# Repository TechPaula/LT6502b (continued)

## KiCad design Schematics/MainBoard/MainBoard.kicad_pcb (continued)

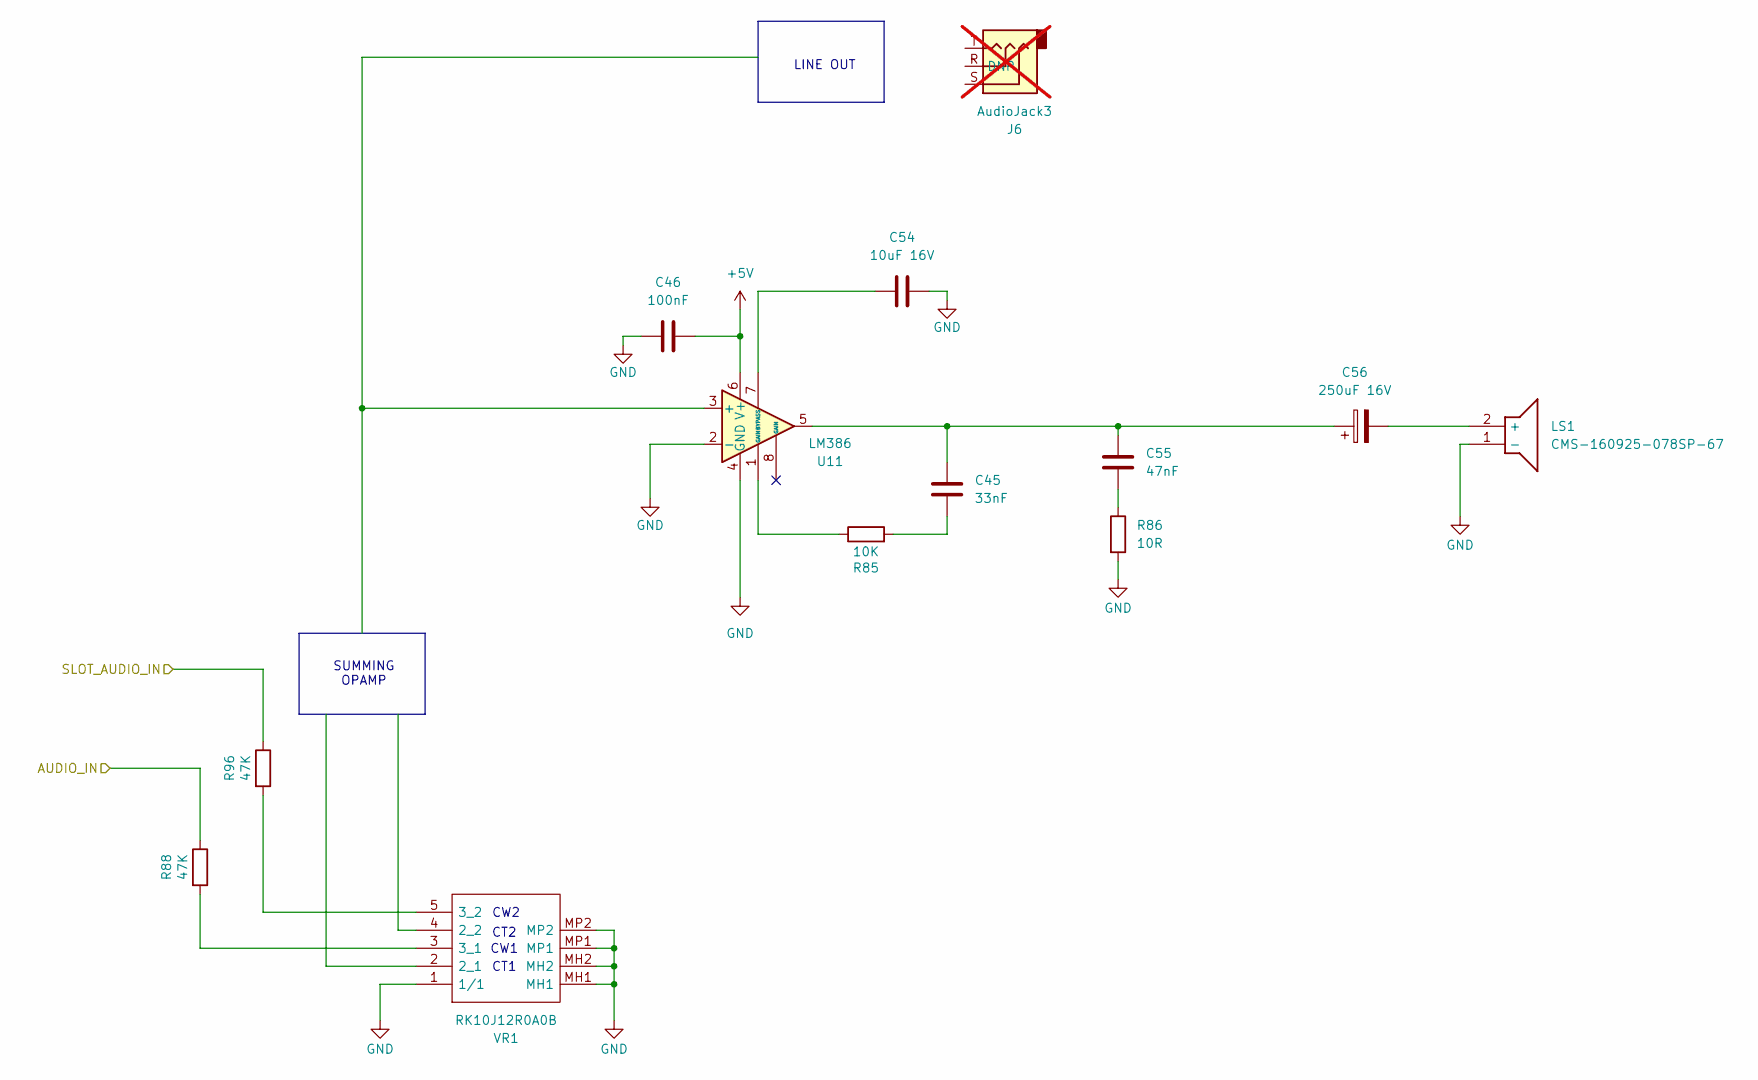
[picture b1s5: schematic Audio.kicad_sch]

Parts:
C45: 33nF; C_0603_1608Metric; LCSC C21117
C46: 100nF; C_0603_1608Metric; LCSC C113803
C54: 10uF 16V; C_0805_2012Metric; LCSC C15850
C55: 47nF; C_0603_1608Metric; LCSC C1622
C56: 250uF 16V; CP_Elec_10x12.5; Mouser Part Number 667-EEV-FK1V681Q
J6: AudioJack3; Jack_3.5mm_CUI_SJ-3524-SMT_Horizontal; LCSC DNP; not fitted
LS1: CMS-160925-078SP-67; CMS160925078SP67; Mouser Part Number 490-CMS160925078SP67
R85: 10K; R_0402_1005Metric; LCSC C25744
R86: 10R; R_0805_2012Metric; LCSC C844598
R88, R96: 47K; R_0402_1005Metric; LCSC DNF
U11: LM386; DIP-8_W7.62mm; Mouser Part Number 926-LM386N-3/NOPB
VR1: RK10J12R0A0B; Mouser Part Number 688-RK10J12R0A0B

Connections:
+5V: C46.2, U11.6 (V+); also elsewhere on the board
AUDIO: R88.1; also elsewhere on the board
GND: C46.1, C54.1, LS1.1 (-), R86.2, U11.2 (-), U11.4 (GND), VR1.1 (1/1), VR1.MH1, VR1.MH2, VR1.MP1, VR1.MP2; also elsewhere on the board
unnamed: C45.1, C55.1, C56.1, U11.5
unnamed: C45.2, R85.2
unnamed: C55.2, R86.1
unnamed: C56.2, LS1.2 (+)
unnamed: R85.1, U11.1 (GAIN)
unnamed: C54.2, U11.7 (BYPASS)
unnamed: R88.2, VR1.3 (3_1)
unnamed: R96.2, VR1.5 (3_2)
SLOT_AUDIO: R96.1; also elsewhere on the board

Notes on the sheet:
CT1
CT2
CW1
CW2
LINE OUT
SUMMING OPAMP

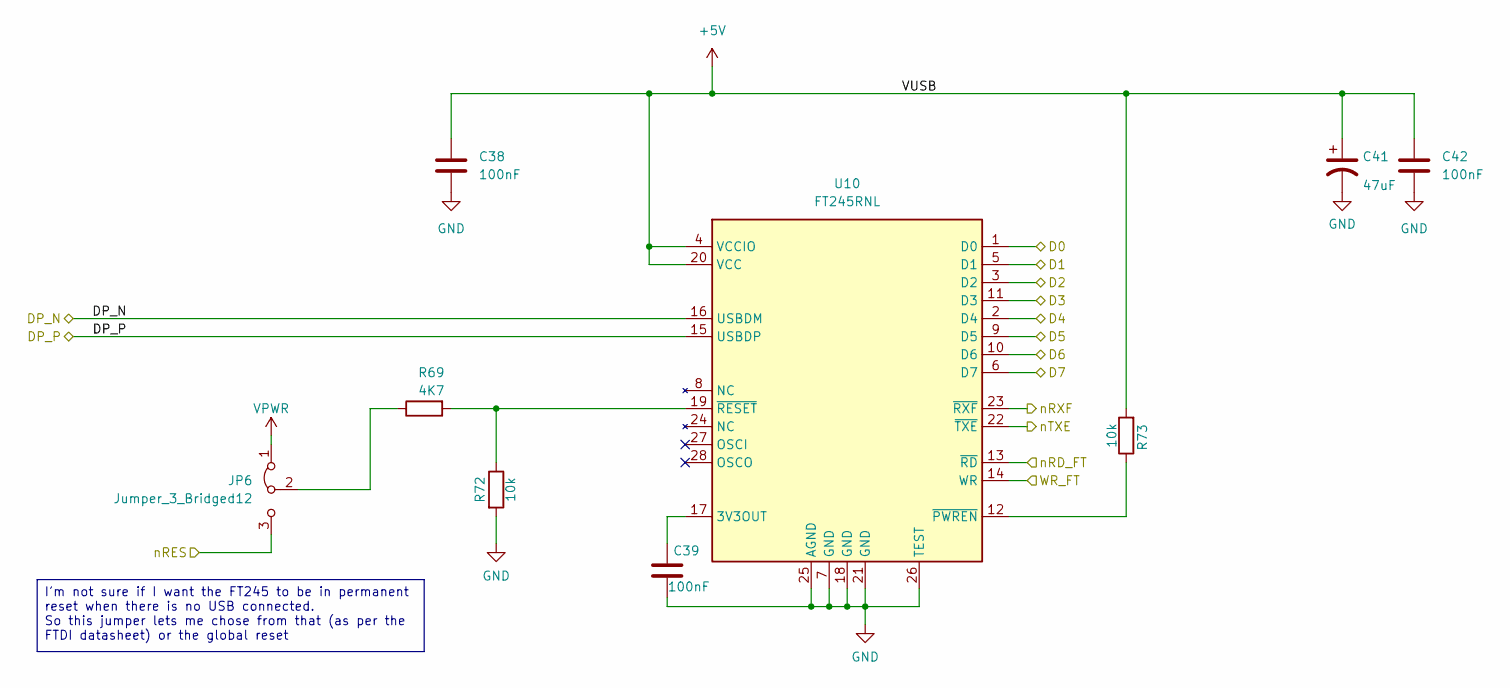
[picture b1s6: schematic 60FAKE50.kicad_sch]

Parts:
C38, C42: 100nF; C_0805_2012Metric; LCSC C49678
C39: 100nF; C_0603_1608Metric; LCSC C113803
C41: 47uF; C_1206_3216Metric; LCSC C22367835
JP6: Jumper_3_Bridged12; SolderJumper-3_P1.3mm_Bridged2Bar12_RoundedPad1.0x1.5mm
R69: 4K7; R_0402_1005Metric
R72, R73: 10k; R_0402_1005Metric; LCSC C25744
U10: FT245RNL; SSOP-28_5.3x10.2mm_P0.65mm; Mouser Part Number 895-FT245RNL-REEL; LCSC DNF

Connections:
+5V: C38.1, C41.1, C42.1, R73.2, U10.4 (VCCIO), U10.20 (VCC); also elsewhere on the board
/60FAKE50/nRES: JP6.3 (B)
/D0: U10.1 (D0); also elsewhere on the board
/D1: U10.5 (D1); also elsewhere on the board
/D2: U10.3 (D2); also elsewhere on the board
/D3: U10.11 (D3); also elsewhere on the board
/D4: U10.2 (D4); also elsewhere on the board
/D5: U10.9 (D5); also elsewhere on the board
/D6: U10.10 (D6); also elsewhere on the board
/D7: U10.6 (D7); also elsewhere on the board
DP_N: U10.16 (USBDM); also elsewhere on the board
DP_P: U10.15 (USBDP); also elsewhere on the board
GND: C38.2, C39.2, C41.2, C42.2, R72.2, U10.7 (GND), U10.18 (GND), U10.21 (GND), U10.25 (AGND), U10.26 (TEST); also elsewhere on the board
unnamed: JP6.2 (C), R69.1
unnamed: C39.1, U10.17 (3V3OUT)
unnamed: R73.1, U10.12 (~PWREN)
unnamed: R69.2, R72.1, U10.19 (~RESET)
VPWR: JP6.1 (A); also elsewhere on the board
WR_FT: U10.14 (WR); also elsewhere on the board
nRD_FT: U10.13 (~RD); also elsewhere on the board
nRXF: U10.23 (~RXF); also elsewhere on the board
nTXE: U10.22 (~TXE); also elsewhere on the board

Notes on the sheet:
I'm not sure if I want the FT245 to be in permanent reset when there is no USB connected. So this jumper lets me chose from that (as per the FTDI datasheet) or the global reset

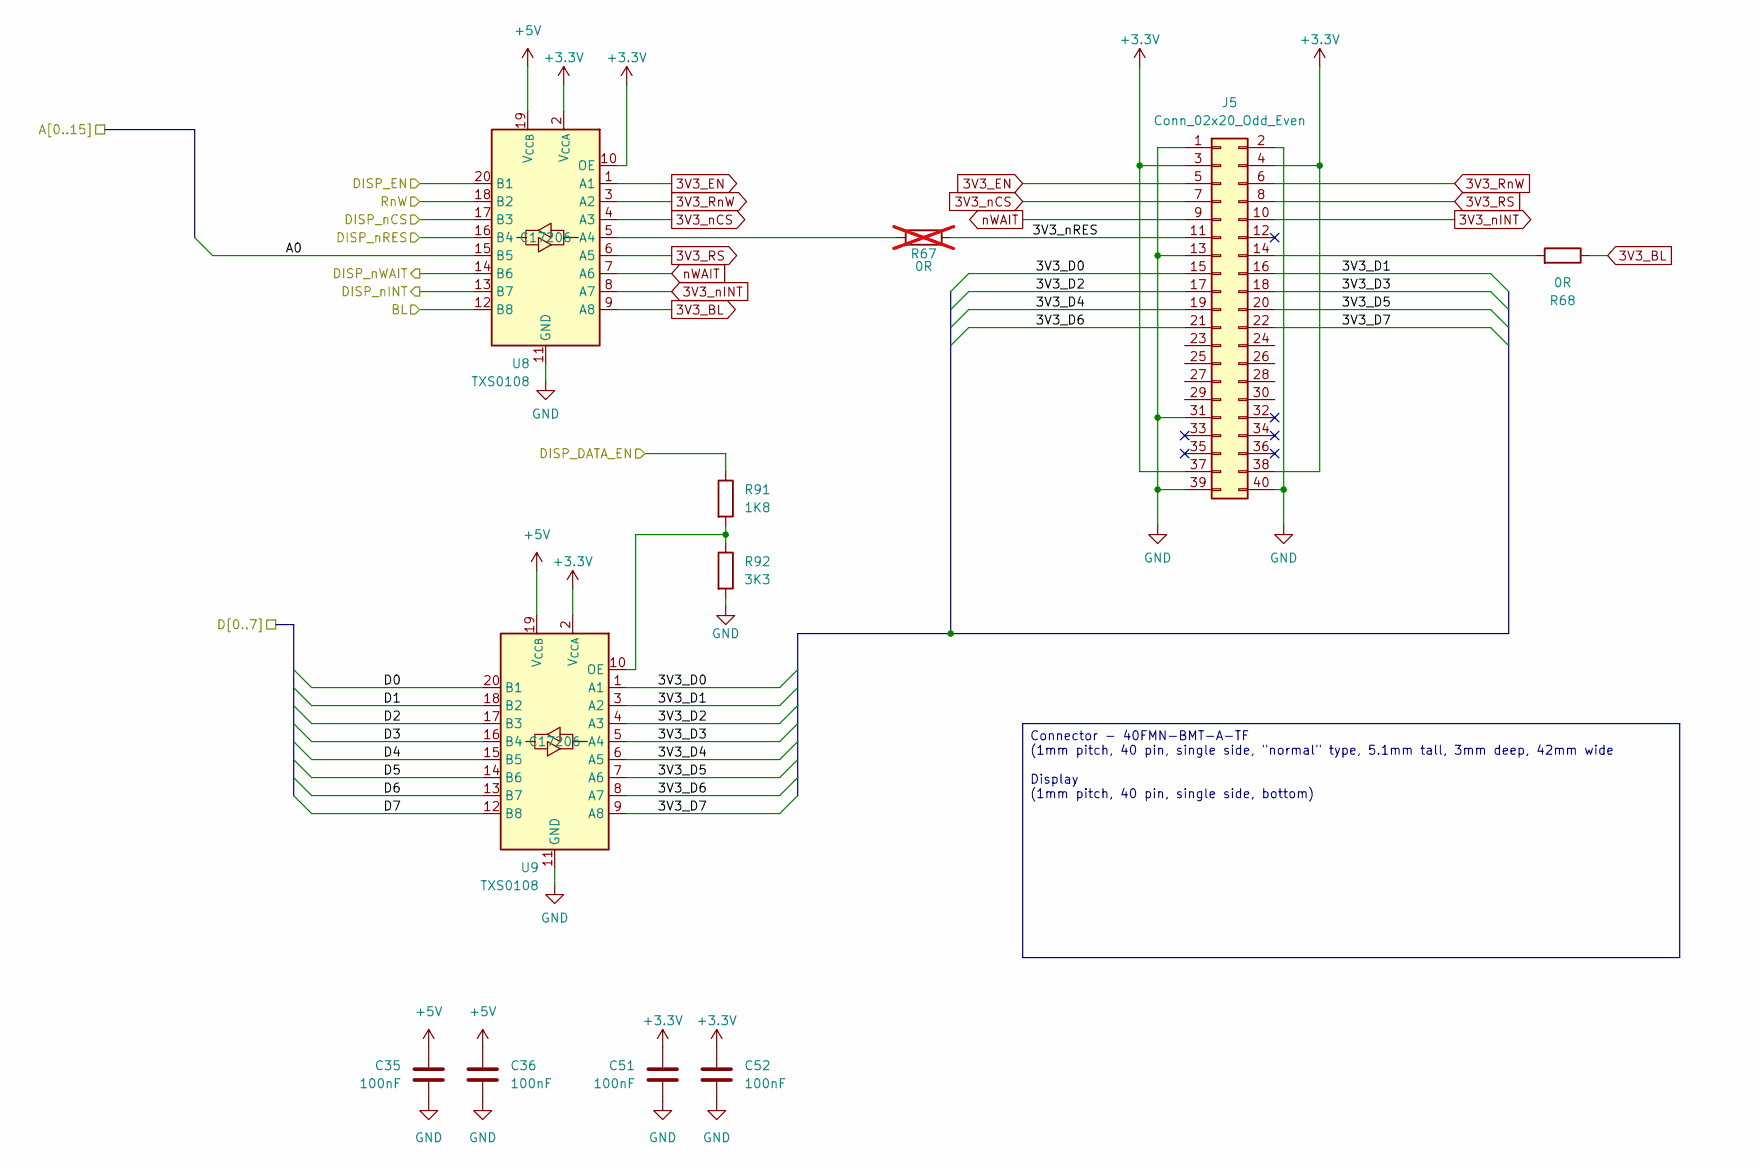
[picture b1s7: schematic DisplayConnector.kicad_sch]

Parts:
C35, C36, C51, C52: 100nF; C_0603_1608Metric; LCSC C113803
J5: Conn_02x20_Odd_Even; GCT_FFC3B07-40-T; LCSC DNF
R67: 0R; R_0402_1005Metric; LCSC DNF; not fitted
R68: 0R; R_0402_1005Metric; LCSC DNF
R91: 1K8; R_0603_1608Metric; LCSC C25890
R92: 3K3; R_0603_1608Metric; LCSC C25890
U8, U9: TXS0108; TSSOP-20_4.4x6.5mm_P0.65mm; Mouser Part Number 595-TXB0108PWR; LCSC C17206

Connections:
3V3_BL: R68.1, U8.9 (A8)
3V3_EN: J5.5, U8.1 (A1)
3V3_RS: J5.8, U8.6 (A5)
3V3_RnW: J5.6, U8.3 (A2)
3V3_nCS: J5.7, U8.4 (A3)
3V3_nINT: J5.10, U8.8 (A7)
+3.3V: C51.1, C52.1, J5.3, J5.4, J5.37, J5.38, U8.2 (V_{CCA}), U8.10 (OE), U9.2 (V_{CCA}); also elsewhere on the board
+5V: C35.1, C36.1, U8.19 (V_{CCB}), U9.19 (V_{CCB}); also elsewhere on the board
/A0: U8.15 (B5); also elsewhere on the board
/D0: U9.20 (B1); also elsewhere on the board
/D1: U9.18 (B2); also elsewhere on the board
/D2: U9.17 (B3); also elsewhere on the board
/D3: U9.16 (B4); also elsewhere on the board
/D4: U9.15 (B5); also elsewhere on the board
/D5: U9.14 (B6); also elsewhere on the board
/D6: U9.13 (B7); also elsewhere on the board
/D7: U9.12 (B8); also elsewhere on the board
/Display Connector/3V3_D0: J5.15, U9.1 (A1)
/Display Connector/3V3_D1: J5.16, U9.3 (A2)
/Display Connector/3V3_D2: J5.17, U9.4 (A3)
/Display Connector/3V3_D3: J5.18, U9.5 (A4)
/Display Connector/3V3_D4: J5.19, U9.6 (A5)
/Display Connector/3V3_D5: J5.20, U9.7 (A6)
/Display Connector/3V3_D6: J5.21, U9.8 (A7)
/Display Connector/3V3_D7: J5.22, U9.9 (A8)
/Display Connector/3V3_nRES: J5.11, R67.2
/Display Connector/BL: U8.12 (B8); also elsewhere on the board
/Display Connector/DISP_DATA_EN: R91.1; also elsewhere on the board
/Display Connector/DISP_EN: U8.20 (B1); also elsewhere on the board
/Display Connector/DISP_nCS: U8.17 (B3); also elsewhere on the board
/Display Connector/DISP_nINT: U8.13 (B7); also elsewhere on the board
/Display Connector/DISP_nRES: U8.16 (B4); also elsewhere on the board
/Display Connector/DISP_nWAIT: U8.14 (B6); also elsewhere on the board
GND: C35.2, C36.2, C51.2, C52.2, J5.1, J5.2, J5.13, J5.31, J5.39, J5.40, R92.2, U8.11 (GND), U9.11 (GND); also elsewhere on the board
unnamed: J5.14, R68.2
unnamed: R67.1, U8.5 (A4)
unnamed: R91.2, R92.1, U9.10 (OE)
RnW: U8.18 (B2); also elsewhere on the board
nWAIT: J5.9, U8.7 (A6)

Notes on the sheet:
Connector - 40FMN-BMT-A-TF (1mm pitch, 40 pin, single side, "normal" type, 5.1mm tall, 3mm deep, 42mm wide Display (1mm pitch, 40 pin, single side, bottom)

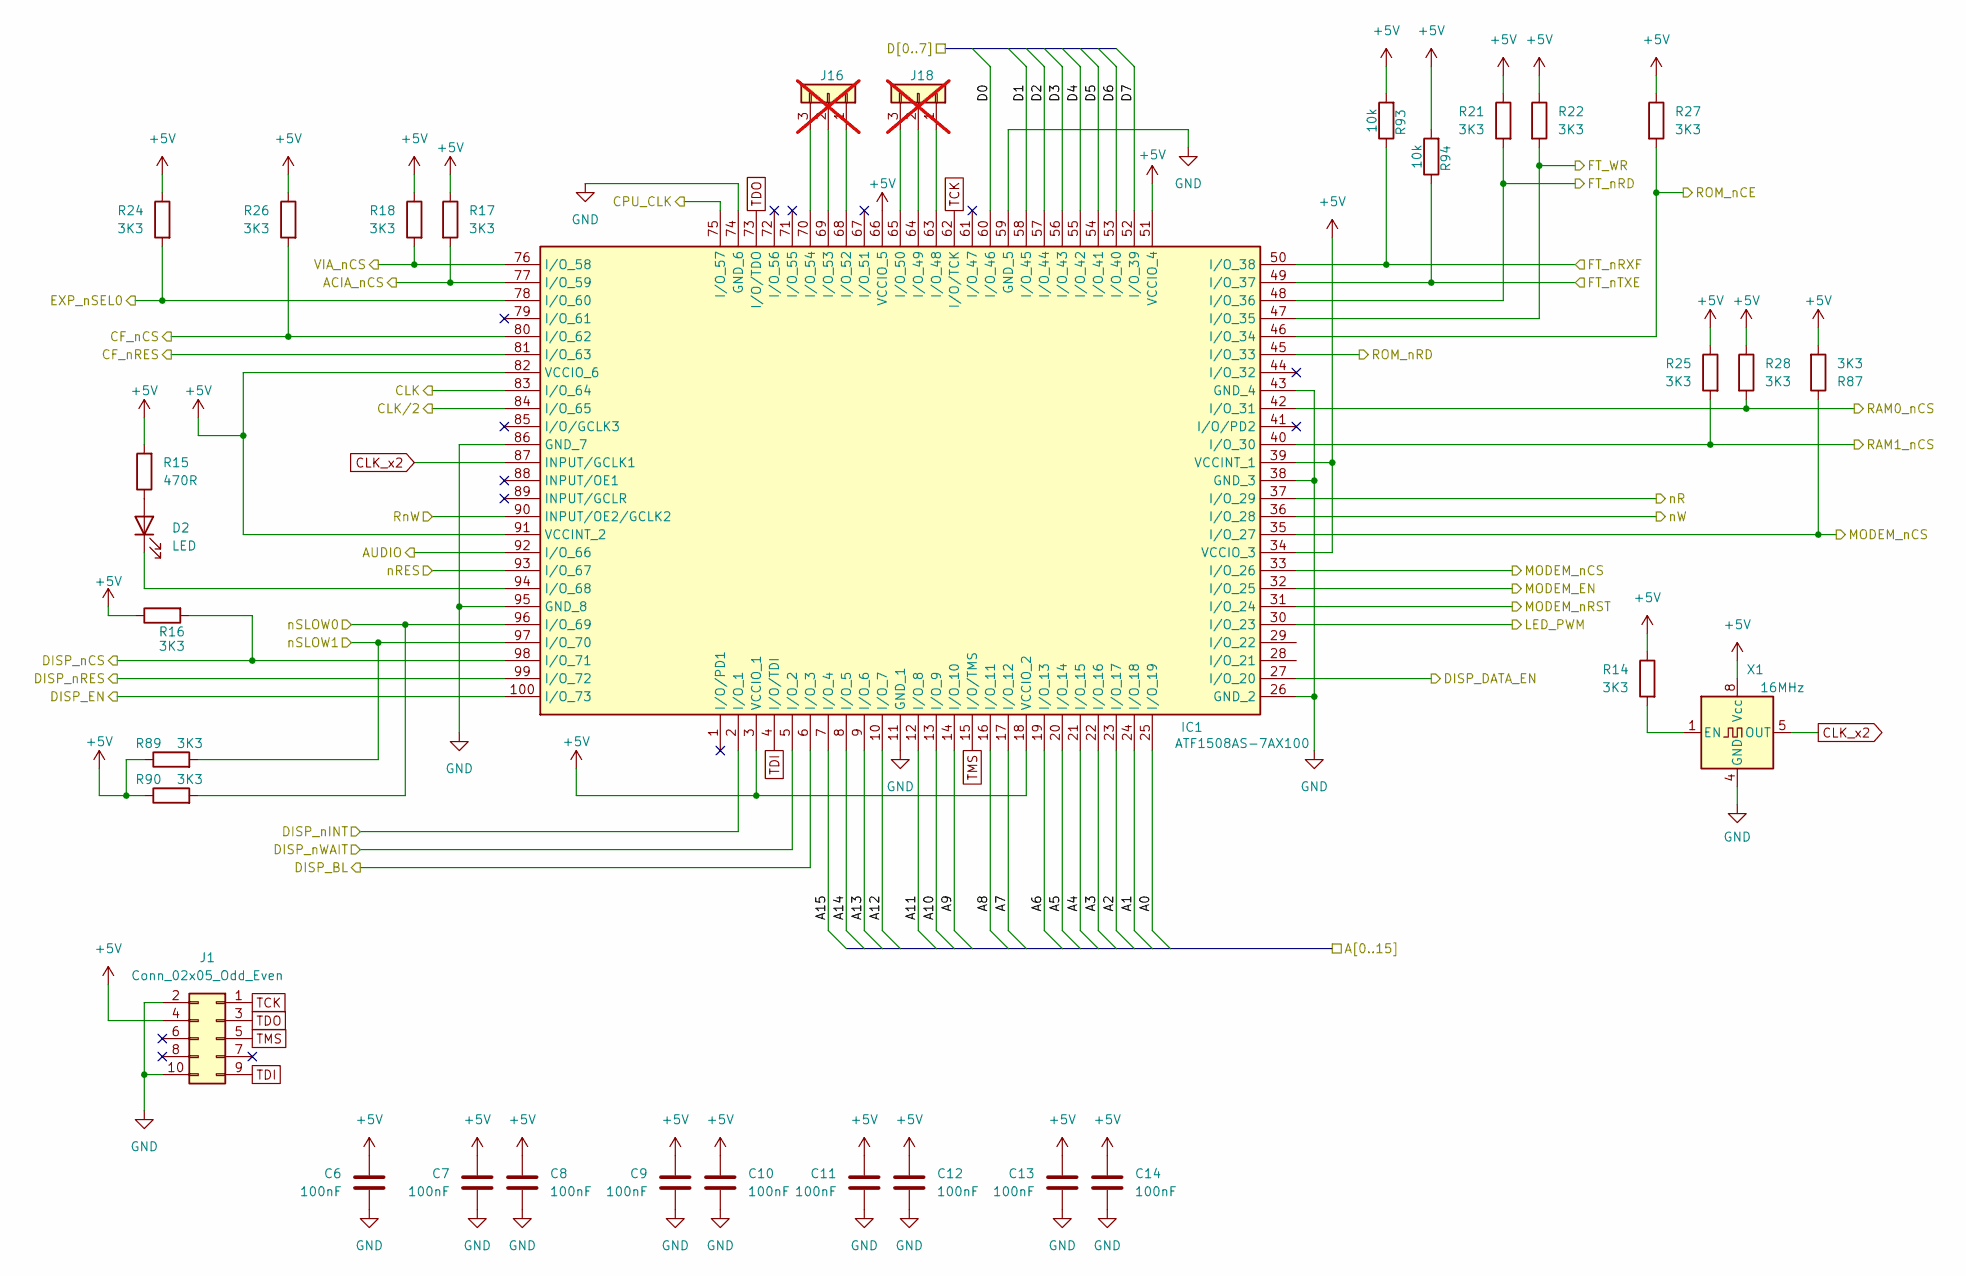
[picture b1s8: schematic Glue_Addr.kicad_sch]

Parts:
C6, C7, C8, C9, C11, C12, C13, C14: 100nF; C_0603_1608Metric; LCSC C113803
C10: 100nF; C_0402_1005Metric; LCSC C1581
D2: LED; LED_0603_1608Metric; LCSC DNF
IC1: ATF1508AS-7AX100; QFP50P1600X1600X120-100N; Mouser Part Number 556-AF1508AS7AX100
J1: Conn_02x05_Odd_Even; PinHeader_2x05_P2.54mm_Vertical; LCSC DNF
J16, J18: Conn_01x03; PinHeader_1x03_P1.00mm_Vertical_SMD_Pin1Left; LCSC DNF; not fitted
R14, R16, R17, R18, R21, R22, R24, R25, R26, R27, R28, R87, R89, R90: 3K3; R_0402_1005Metric; LCSC C25890
R15: 470R; R_0402_1005Metric; LCSC C25117
R93, R94: 10k; R_0402_1005Metric; LCSC C25744
X1: 16MHz; Oscillator_DIP-8; Mouser Part Number 520-2100AX-283.2; LCSC DNF

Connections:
+5V: C6.1, C7.1, C8.1, C9.1, C10.1, C11.1, C12.1, C13.1, C14.1, IC1.3 (VCCIO_1), IC1.18 (VCCIO_2), IC1.34 (VCCIO_3), IC1.39 (VCCINT_1), IC1.51 (VCCIO_4), IC1.66 (VCCIO_5), IC1.82 (VCCIO_6), IC1.91 (VCCINT_2), J1.4, R14.1, R15.2, R16.1, R17.1, R18.1, R21.1, R22.1, R24.1, R25.1, R26.1, R27.1, R28.1, R87.2, R89.1, R90.1, R93.2, R94.2, X1.8 (Vcc); also elsewhere on the board
/A0: IC1.25 (I/O_19); also elsewhere on the board
/A1: IC1.24 (I/O_18); also elsewhere on the board
/A2: IC1.23 (I/O_17); also elsewhere on the board
/A3: IC1.22 (I/O_16); also elsewhere on the board
/A4: IC1.21 (I/O_15); also elsewhere on the board
/A5: IC1.20 (I/O_14); also elsewhere on the board
/A6: IC1.19 (I/O_13); also elsewhere on the board
/A7: IC1.17 (I/O_12); also elsewhere on the board
/A8: IC1.16 (I/O_11); also elsewhere on the board
/A9: IC1.14 (I/O_10); also elsewhere on the board
/A10: IC1.13 (I/O_9); also elsewhere on the board
/A11: IC1.12 (I/O_8); also elsewhere on the board
/A12: IC1.10 (I/O_7); also elsewhere on the board
/A13: IC1.9 (I/O_6); also elsewhere on the board
/A14: IC1.8 (I/O_5); also elsewhere on the board
/A15: IC1.7 (I/O_4); also elsewhere on the board
/D0: IC1.60 (I/O_46); also elsewhere on the board
/D1: IC1.58 (I/O_45); also elsewhere on the board
/D2: IC1.57 (I/O_44); also elsewhere on the board
/D3: IC1.56 (I/O_43); also elsewhere on the board
/D4: IC1.55 (I/O_42); also elsewhere on the board
/D5: IC1.54 (I/O_41); also elsewhere on the board
/D6: IC1.53 (I/O_40); also elsewhere on the board
/D7: IC1.52 (I/O_39); also elsewhere on the board
/Display Connector/BL: IC1.6 (I/O_3); also elsewhere on the board
/Display Connector/DISP_DATA_EN: IC1.27 (I/O_20); also elsewhere on the board
/Display Connector/DISP_EN: IC1.100 (I/O_73); also elsewhere on the board
/Display Connector/DISP_nCS: IC1.98 (I/O_71), R16.2; also elsewhere on the board
/Display Connector/DISP_nINT: IC1.2 (I/O_1); also elsewhere on the board
/Display Connector/DISP_nRES: IC1.99 (I/O_72); also elsewhere on the board
/Display Connector/DISP_nWAIT: IC1.5 (I/O_2); also elsewhere on the board
ACIA_nCS: IC1.77 (I/O_59), R17.2; also elsewhere on the board
AUDIO: IC1.92 (I/O_66); also elsewhere on the board
CFnRES: IC1.80 (I/O_62), R26.2; also elsewhere on the board
CLK: IC1.83 (I/O_64); also elsewhere on the board
CLK_x2: IC1.87 (INPUT/GCLK1), X1.5 (OUT)
CLK/2: IC1.84 (I/O_65); also elsewhere on the board
CPU_CLK: IC1.75 (I/O_57); also elsewhere on the board
EXP_nSEL0: IC1.78 (I/O_60), R24.2; also elsewhere on the board
GND: C6.2, C7.2, C8.2, C9.2, C10.2, C11.2, C12.2, C13.2, C14.2, IC1.11 (GND_1), IC1.26 (GND_2), IC1.38 (GND_3), IC1.43 (GND_4), IC1.59 (GND_5), IC1.74 (GND_6), IC1.86 (GND_7), IC1.95 (GND_8), J1.2, J1.10, X1.4 (GND); also elsewhere on the board
KEYLED_PWM: IC1.30 (I/O_23); also elsewhere on the board
MODEM_EN: IC1.32 (I/O_25); also elsewhere on the board
MODEM_nCS: IC1.33 (I/O_26), IC1.35 (I/O_27), R87.1; also elsewhere on the board
MODEM_nRST: IC1.31 (I/O_24); also elsewhere on the board
unnamed: D2.2 (A), R15.1
unnamed: D2.1 (K), IC1.94 (I/O_68)
unnamed: IC1.63 (I/O_48), J18.1
unnamed: IC1.64 (I/O_49), J18.2
unnamed: IC1.65 (I/O_50), J18.3
unnamed: IC1.68 (I/O_52), J16.1
unnamed: IC1.69 (I/O_53), J16.2
unnamed: IC1.70 (I/O_54), J16.3
unnamed: R14.2, X1.1 (EN)
ROM_nCE: IC1.46 (I/O_34), R27.2; also elsewhere on the board
ROM_nR: IC1.45 (I/O_33); also elsewhere on the board
RnW: IC1.90 (INPUT/OE2/GCLK2); also elsewhere on the board
TCK: IC1.62 (I/O/TCK), J1.1
TDI: IC1.4 (I/O/TDI), J1.9
TDO: IC1.73 (I/O/TDO), J1.3
TMS: IC1.15 (I/O/TMS), J1.5
VIA_nCS: IC1.76 (I/O_58), R18.2; also elsewhere on the board
WR_FT: IC1.47 (I/O_35), R22.2; also elsewhere on the board
nCF_CS0: IC1.81 (I/O_63); also elsewhere on the board
nR: IC1.37 (I/O_29); also elsewhere on the board
nRAM0_CS: IC1.42 (I/O_31), R28.2; also elsewhere on the board
nRAM1_CS: IC1.40 (I/O_30), R25.2; also elsewhere on the board
nRD_FT: IC1.48 (I/O_36), R21.2; also elsewhere on the board
nRES: IC1.93 (I/O_67); also elsewhere on the board
nRXF: IC1.49 (I/O_37), R94.1; also elsewhere on the board
nSLOW0: IC1.96 (I/O_69), R90.2; also elsewhere on the board
nSLOW1: IC1.97 (I/O_70), R89.2; also elsewhere on the board
nTXE: IC1.50 (I/O_38), R93.1; also elsewhere on the board
nW: IC1.36 (I/O_28); also elsewhere on the board

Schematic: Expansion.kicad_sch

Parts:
C43: 100nF; C_0603_1608Metric; LCSC C113803
C44: 22uF 25V; C_0805_2012Metric; LCSC C45783
D19, D21: 1N4148; D_DO-35_SOD27_P7.62mm_Horizontal; LCSC DNF
J10: Conn_02x20_Odd_Even; PinHeader_2x20_P2.54mm_Horizontal

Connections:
+5V: C43.1, C44.1, J10.1, J10.2, J10.3, J10.4; also elsewhere on the board
/A0: J10.5; also elsewhere on the board
/A1: J10.6; also elsewhere on the board
/A2: J10.7; also elsewhere on the board
/A3: J10.8; also elsewhere on the board
/A4: J10.9; also elsewhere on the board
/A5: J10.10; also elsewhere on the board
/A6: J10.11; also elsewhere on the board
/A7: J10.12; also elsewhere on the board
/D0: J10.13; also elsewhere on the board
/D1: J10.14; also elsewhere on the board
/D2: J10.15; also elsewhere on the board
/D3: J10.16; also elsewhere on the board
/D4: J10.17; also elsewhere on the board
/D5: J10.18; also elsewhere on the board
/D6: J10.19; also elsewhere on the board
/D7: J10.20; also elsewhere on the board
CLK: J10.28; also elsewhere on the board
CLK/2: J10.30; also elsewhere on the board
CPU_CLK: J10.23; also elsewhere on the board
EXP_nSEL0: J10.31; also elsewhere on the board
GND: C43.2, C44.2, J10.37, J10.38, J10.39, J10.40; also elsewhere on the board
unnamed: D19.1 (K), J10.27
unnamed: D21.1 (K), J10.29
RnW: J10.24; also elsewhere on the board
SLOT_AUDIO: J10.36; also elsewhere on the board
nIRQ: J10.32; also elsewhere on the board
nRES: J10.33; also elsewhere on the board
nSLOW0: D19.2 (A); also elsewhere on the board
nSLOW1: D21.2 (A); also elsewhere on the board

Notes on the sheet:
I should have routed CLK/2 to the VIA/ACIA instead of the 16MHz Clock So I've swapped them in the CPLD.
Much simplified from first laptop This is solely for expansion now and not an alternative CPU

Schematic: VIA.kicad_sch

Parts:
C47: 100nF; C_0402_1005Metric; LCSC C113803
D16: 1N4148W; D_SOD-123; LCSC C2099
IC3: W65C22S6TQG-14; QFP80P1320X1320X270-44N; Mouser Part Number 955-W65C22S6TQG-14
J9: Conn_02x02_Odd_Even; PinHeader_2x02_P1.27mm_Vertical_SMD
J12, J13: Conn_02x06_Odd_Even; PinSocket_2x06_P2.54mm_Horizontal; LCSC DNF

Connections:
+5V: C47.1, IC3.15 (VDD), IC3.20 (CS1), J12.1, J12.2, J13.1, J13.2; also elsewhere on the board
/A0: IC3.36 (RS0); also elsewhere on the board
/A1: IC3.35 (RS1); also elsewhere on the board
/A2: IC3.34 (RS2); also elsewhere on the board
/A3: IC3.33 (RS3); also elsewhere on the board
/D0: IC3.30 (D0); also elsewhere on the board
/D1: IC3.29 (D1); also elsewhere on the board
/D2: IC3.28 (D2); also elsewhere on the board
/D3: IC3.26 (D3); also elsewhere on the board
/D4: IC3.25 (D4); also elsewhere on the board
/D5: IC3.24 (D5); also elsewhere on the board
/D6: IC3.23 (D6); also elsewhere on the board
/D7: IC3.22 (D7); also elsewhere on the board
/VIA/VA_CA1: IC3.37 (CA2), J9.1; also elsewhere on the board
/VIA/VA_CA2: IC3.38 (CA1), J9.3; also elsewhere on the board
/VIA/VA_CB1: IC3.13 (CB1), J9.2; also elsewhere on the board
/VIA/VA_CB2: IC3.14 (CB2), J9.4; also elsewhere on the board
/VIA/VA_PA0: IC3.40 (PA0), J13.11
/VIA/VA_PA1: IC3.41 (PA1), J13.9
/VIA/VA_PA2: IC3.42 (PA2), J13.7
/VIA/VA_PA3: IC3.43 (PA3), J13.5
/VIA/VA_PA4: IC3.44 (PA4), J13.12
/VIA/VA_PA5: IC3.1 (PA5), J13.10
/VIA/VA_PA6: IC3.2 (PA6), J13.8
/VIA/VA_PA7: IC3.3 (PA7), J13.6
/VIA/VA_PB0: IC3.4 (PB0), J12.11
/VIA/VA_PB1: IC3.6 (PB1), J12.9
/VIA/VA_PB2: IC3.7 (PB2), J12.7
/VIA/VA_PB3: IC3.8 (PB3), J12.5
/VIA/VA_PB4: IC3.9 (PB4), J12.12
/VIA/VA_PB5: IC3.10 (PB5), J12.10
/VIA/VA_PB6: IC3.11 (PB6), J12.8
/VIA/VA_PB7: IC3.12 (PB7), J12.6
CLK: IC3.21 (PHI2); also elsewhere on the board
GND: C47.2, IC3.39 (VSS), J12.3, J12.4, J13.3, J13.4; also elsewhere on the board
unnamed: D16.1 (K), IC3.17 (IRQB)
RnW: IC3.18 (IRWB); also elsewhere on the board
VIA_nCS: IC3.19 (CS2B); also elsewhere on the board
nIRQ: D16.2 (A); also elsewhere on the board
nRES: IC3.31 (RESB); also elsewhere on the board

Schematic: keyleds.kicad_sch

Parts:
D17: LED; LED_D5.0mm; LCSC DNF
D56, D60, D61, D62, D63, D64, D65, D66, D67, D68: LED; LED_0603_1608Metric; LCSC C3030991
JP4: Jumper_3_Bridged12; SolderJumper-3_P1.3mm_Bridged2Bar12_RoundedPad1.0x1.5mm
JP5: Jumper_2_Open; SolderJumper-2_P1.3mm_Open_TrianglePad1.0x1.5mm; LCSC DNF
R70: 470R; R_0603_1608Metric_Pad0.98x0.95mm_HandSolder; LCSC DNF
R107, R115, R116, R117, R118, R119, R120, R121, R122, R123: 330R; R_0603_1608Metric_Pad0.98x0.95mm_HandSolder; LCSC DNF

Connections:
+5V: JP4.3 (B); also elsewhere on the board
/Keyboard IF/KEY_LEDs/LED_PWM: D56.2 (A), D60.2 (A), D61.2 (A), D62.2 (A), D63.2 (A), D64.2 (A), JP4.1 (A), JP5.1 (A); also elsewhere on the board
GND: R107.1, R115.1, R116.1, R117.1, R118.1, R119.1, R120.1, R121.1, R122.1, R123.1; also elsewhere on the board
KEYLED0: D17.1 (K); also elsewhere on the board
unnamed: D17.2 (A), R70.2
unnamed: D56.1 (K), R107.2
unnamed: D60.1 (K), R115.2
unnamed: D61.1 (K), R116.2
unnamed: D62.1 (K), R117.2
unnamed: D63.1 (K), R118.2
unnamed: D64.1 (K), R119.2
unnamed: D65.2 (A), D66.2 (A), D67.2 (A), D68.2 (A), JP5.2 (B)
unnamed: D65.1 (K), R120.2
unnamed: D66.1 (K), R121.2
unnamed: D67.1 (K), R122.2
unnamed: D68.1 (K), R123.2
unnamed: JP4.2 (C), R70.1

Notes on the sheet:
LEFT
ENTER
SHIFT
RIGHT
BREAK
BACKSPACE
CTRL
DOWN

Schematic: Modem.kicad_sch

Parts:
C60, C62, C63: 100nF; C_0402_1005Metric; LCSC C113803
C61: 47uF; C_1206_3216Metric; LCSC C96123
R97, R98, R101, R104: 10K; R_0402_1005Metric; LCSC DNF; not fitted
R99, R102: 1K8; R_0603_1608Metric; LCSC C25890
R100, R103: 3K3; R_0603_1608Metric; LCSC C25890
R105, R106: 0R; R_0603_1608Metric
U13: ESP8266-01_ESP-01; XCVR_ESP8266-01_ESP-01; PARTREV V1.2
U14: TXS0102DCT; SSOP-8_2.95x2.8mm_P0.65mm

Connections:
+3.3V: C60.1, C61.1, C62.1, R97.1, R98.1, U13.8 (VCC), U14.3 (VCCA), U14.6 (OE); also elsewhere on the board
+5V: C63.1, R101.1, R104.1, U14.7 (VCCB); also elsewhere on the board
/Keyboard IF/Modem/RX_3V3: R98.2, U13.4 (RXD), U14.4 (A2)
/Keyboard IF/Modem/TX_3V3: R97.2, U13.5 (TXD), U14.5 (A1)
GND: C60.2, C61.2, C62.2, C63.2, R100.2, R103.2, U13.1 (GND), U14.2 (GND); also elsewhere on the board
MODEM_EN: R99.1; also elsewhere on the board
MODEM_SER_IN: R105.2; also elsewhere on the board
MODEM_SER_OUT: R106.2; also elsewhere on the board
MODEM_nRST: R102.1; also elsewhere on the board
unnamed: R99.2, R100.1, U13.6 (EN)
unnamed: R102.2, R103.1, U13.7 (~RST)
unnamed: R101.2, R105.1, U14.8 (B1)
unnamed: R104.2, R106.1, U14.1 (B2)

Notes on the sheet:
Place to allow RX/TX swap

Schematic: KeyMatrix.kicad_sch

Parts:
D1, D12, D13, D14, D15, D20, D22, D23, D24, D25, D26, D27, D28, D29, D30, D31, D32, D33, D34, D35, D36, D37, D38, D39, D40, D41, D42, D43, D44, D45, D46, D47, D48, D49, D50, D51, D52, D53, D54, D55, D57, D58, D59, D69, D70, D71, D72, D73, D74, D75, D76, D77, D78, D79, D80, D81, D82, D83: 1N4148W; D_SOD-123; LCSC C2099
SW1, SW2, SW3, SW4, SW5, SW6, SW7, SW8, SW9, SW10, SW11, SW12, SW13, SW14, SW15, SW16, SW17, SW18, SW19, SW20, SW21, SW22, SW23, SW24, SW25, SW26, SW27, SW28, SW29, SW30, SW31, SW32, SW33, SW34, SW35, SW36, SW37, SW38, SW39, SW40, SW41, SW42, SW43, SW44, SW45, SW46, SW47, SW48, SW49, SW50, SW51, SW52, SW53, SW54, SW55, SW57, SW58, SW59, SW60, SW61, SW65: SW_Push; SW_PG1350; LCSC DNF

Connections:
/Keyboard IF/KeyMatrix/COL0: D1.1 (K), D12.1 (K), D13.1 (K), D14.1 (K), D15.1 (K), D20.1 (K), D22.1 (K), D23.1 (K); also elsewhere on the board
/Keyboard IF/KeyMatrix/COL1: D24.1 (K), D25.1 (K), D26.1 (K), D27.1 (K), D28.1 (K), D29.1 (K), D30.1 (K), D31.1 (K); also elsewhere on the board
/Keyboard IF/KeyMatrix/COL2: D32.1 (K), D33.1 (K), D34.1 (K), D35.1 (K), D36.1 (K), D37.1 (K), D38.1 (K), D39.1 (K); also elsewhere on the board
/Keyboard IF/KeyMatrix/COL3: D40.1 (K), D41.1 (K), D42.1 (K), D43.1 (K), D44.1 (K), D45.1 (K), D46.1 (K); also elsewhere on the board
/Keyboard IF/KeyMatrix/COL4: D47.1 (K), D48.1 (K), D49.1 (K), D50.1 (K), D51.1 (K), D52.1 (K), D53.1 (K); also elsewhere on the board
/Keyboard IF/KeyMatrix/COL5: D54.1 (K), D55.1 (K), D57.1 (K), D58.1 (K), D59.1 (K), D69.1 (K), D70.1 (K); also elsewhere on the board
/Keyboard IF/KeyMatrix/COL6: D71.1 (K), D72.1 (K), D73.1 (K), D74.1 (K), D75.1 (K), D76.1 (K), D77.1 (K); also elsewhere on the board
/Keyboard IF/KeyMatrix/COL7: D78.1 (K), D79.1 (K), D80.1 (K), D81.1 (K), D82.1 (K), D83.1 (K); also elsewhere on the board
unnamed: D1.2 (A), SW1.2
unnamed: D12.2 (A), SW9.2
unnamed: D13.2 (A), SW17.2
unnamed: D14.2 (A), SW18.2
unnamed: D15.2 (A), SW33.2
unnamed: D20.2 (A), SW34.2
unnamed: D22.2 (A), SW49.2
unnamed: D23.2 (A), SW57.2
unnamed: D24.2 (A), SW2.2
unnamed: D25.2 (A), SW10.2
unnamed: D26.2 (A), SW19.2
unnamed: D27.2 (A), SW20.2
unnamed: D28.2 (A), SW35.2
unnamed: D29.2 (A), SW36.2
unnamed: D30.2 (A), SW50.2
unnamed: D31.2 (A), SW58.2, SW65.2
unnamed: D32.2 (A), SW59.2
unnamed: D33.2 (A), SW3.2
unnamed: D34.2 (A), SW11.2
unnamed: D35.2 (A), SW21.2
unnamed: D36.2 (A), SW22.2
unnamed: D37.2 (A), SW37.2
unnamed: D38.2 (A), SW38.2
unnamed: D39.2 (A), SW51.2
unnamed: D40.2 (A), SW4.2
unnamed: D41.2 (A), SW12.2
unnamed: D42.2 (A), SW23.2
unnamed: D43.2 (A), SW24.2
unnamed: D44.2 (A), SW39.2
unnamed: D45.2 (A), SW40.2
unnamed: D46.2 (A), SW52.2
unnamed: D47.2 (A), SW5.2
unnamed: D48.2 (A), SW13.2
unnamed: D49.2 (A), SW25.2
unnamed: D50.2 (A), SW26.2
unnamed: D51.2 (A), SW41.2
unnamed: D52.2 (A), SW42.2
unnamed: D53.2 (A), SW53.2
unnamed: D54.2 (A), SW6.2
unnamed: D55.2 (A), SW14.2
unnamed: D57.2 (A), SW27.2
unnamed: D58.2 (A), SW28.2
unnamed: D59.2 (A), SW43.2
unnamed: D69.2 (A), SW44.2
unnamed: D70.2 (A), SW54.2
unnamed: D71.2 (A), SW7.2
unnamed: D72.2 (A), SW15.2
unnamed: D73.2 (A), SW29.2
unnamed: D74.2 (A), SW30.2
unnamed: D75.2 (A), SW45.2
unnamed: D76.2 (A), SW46.2
unnamed: D77.2 (A), SW55.2
unnamed: D78.2 (A), SW8.2
unnamed: D79.2 (A), SW16.2
unnamed: D80.2 (A), SW31.2
unnamed: D81.2 (A), SW32.2
unnamed: D82.2 (A), SW47.2
unnamed: D83.2 (A), SW48.2, SW60.2, SW61.2
ROW0: SW1.1, SW2.1, SW3.1, SW4.1, SW5.1, SW6.1, SW7.1, SW8.1; also elsewhere on the board
ROW1: SW9.1, SW10.1, SW11.1, SW12.1, SW13.1, SW14.1, SW15.1, SW16.1; also elsewhere on the board
ROW2: SW17.1, SW19.1, SW21.1, SW23.1, SW25.1, SW27.1, SW29.1, SW31.1; also elsewhere on the board
ROW3: SW18.1, SW20.1, SW22.1, SW24.1, SW26.1, SW28.1, SW30.1, SW32.1; also elsewhere on the board
ROW4: SW33.1, SW35.1, SW37.1, SW39.1, SW41.1, SW43.1, SW45.1, SW47.1; also elsewhere on the board
ROW5: SW34.1, SW36.1, SW38.1, SW40.1, SW42.1, SW44.1, SW46.1, SW48.1, SW60.1, SW61.1; also elsewhere on the board
ROW6: SW49.1, SW50.1, SW51.1, SW52.1, SW53.1, SW54.1, SW55.1; also elsewhere on the board
ROW7: SW57.1, SW58.1, SW59.1, SW65.1; also elsewhere on the board

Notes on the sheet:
LEFT SHIFT RIGHT SHIFT
A B C D E F G H I J K L M N O P Q R S T U V W X Y Z 0 1 2 3 4 5 6 7 8 9 - = [ ] ; ' # , . / \ sp up dn lf rh dl bk en tb sh ct sp = space bar up = up key dn = down key lf = left key rh = right key dl = delete key bk = break key en = enter key tb = tab key sh = shift key ct = control key

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
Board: 4 copper layers, 396 parts (1 on the bottom side), 318 nets, no tracks yet.

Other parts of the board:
J11: Conn_02x04_Odd_Even; PinSocket_2x04_P2.54mm_Horizontal
JP3: PD LED PWR; SolderJumper-3_P1.3mm_Bridged12_Pad1.0x1.5mm_NumberLabels

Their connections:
+3.3V: JP3.3 (B); also elsewhere on the board
+5V: J11.1, J11.2; also elsewhere on the board
/VIA/VA_CA1: J11.7; also elsewhere on the board
/VIA/VA_CA2: J11.5; also elsewhere on the board
/VIA/VA_CB1: J11.8; also elsewhere on the board
/VIA/VA_CB2: J11.6; also elsewhere on the board
GND: J11.3, J11.4; also elsewhere on the board

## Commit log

2026-02-22 Add models, add basic keyboard shape, update readme
2026-02-22 Moved key
2026-02-22 Add extra mounting holes
2026-02-22 Move holes a little more
2026-02-22 Added files from Fusion
2026-02-22 Added dimensions to drawing
2026-02-22 Work on Main Board Schematic and new board shape
2026-02-22 Updated USB wiring, moved key parts, increased board dimensions
2026-02-24 Move to a single board for everything (keyboard and main board)
    Aim is to save height
2026-02-24 rough placement of parts to help with 3D CAD
2026-02-24 Work on parts placement, remove excess LEDs
2026-02-26 Work on PCB
2026-02-27 Work on main board parts positions
2026-02-27 Updated STEP file with missing parts
2026-02-27 Added image
2026-02-28 Work on PCB routing, added SwinSID
2026-03-01 Completed routing
2026-03-07 Updates based on production files for JLC
2026-03-07 Revise README with project details and updates
    Updated project description and added specifications and features.
2026-03-07 Fix formatting issue in README updates section
2026-03-07 Fix formatting of update entries in README
2026-03-07 Added image of case in progress
2026-03-21 Add some comments to schematic, update README, start on GLUE
    Add some comments to schematic, update README, start on GLUE
2026-03-22 Work on revised firmware and CPLD
2026-03-22 Modify CPLD code & tidy
    CPLD code changed to use FIELD for address, RAM1 now working and code looks a LOT tidier!
2026-03-22 Work on cpld
    CF now working,
    Seems to sometimes crash, unclear why at this stage, possibly a timing issue with console port.
2026-03-22 Add notes to GLUE logic page
2026-03-22 removed RA8875 display parts from Firmware
2026-03-25 Begun work on display (RA8889)
    Basic Register read code working!
2026-03-26 init display work
